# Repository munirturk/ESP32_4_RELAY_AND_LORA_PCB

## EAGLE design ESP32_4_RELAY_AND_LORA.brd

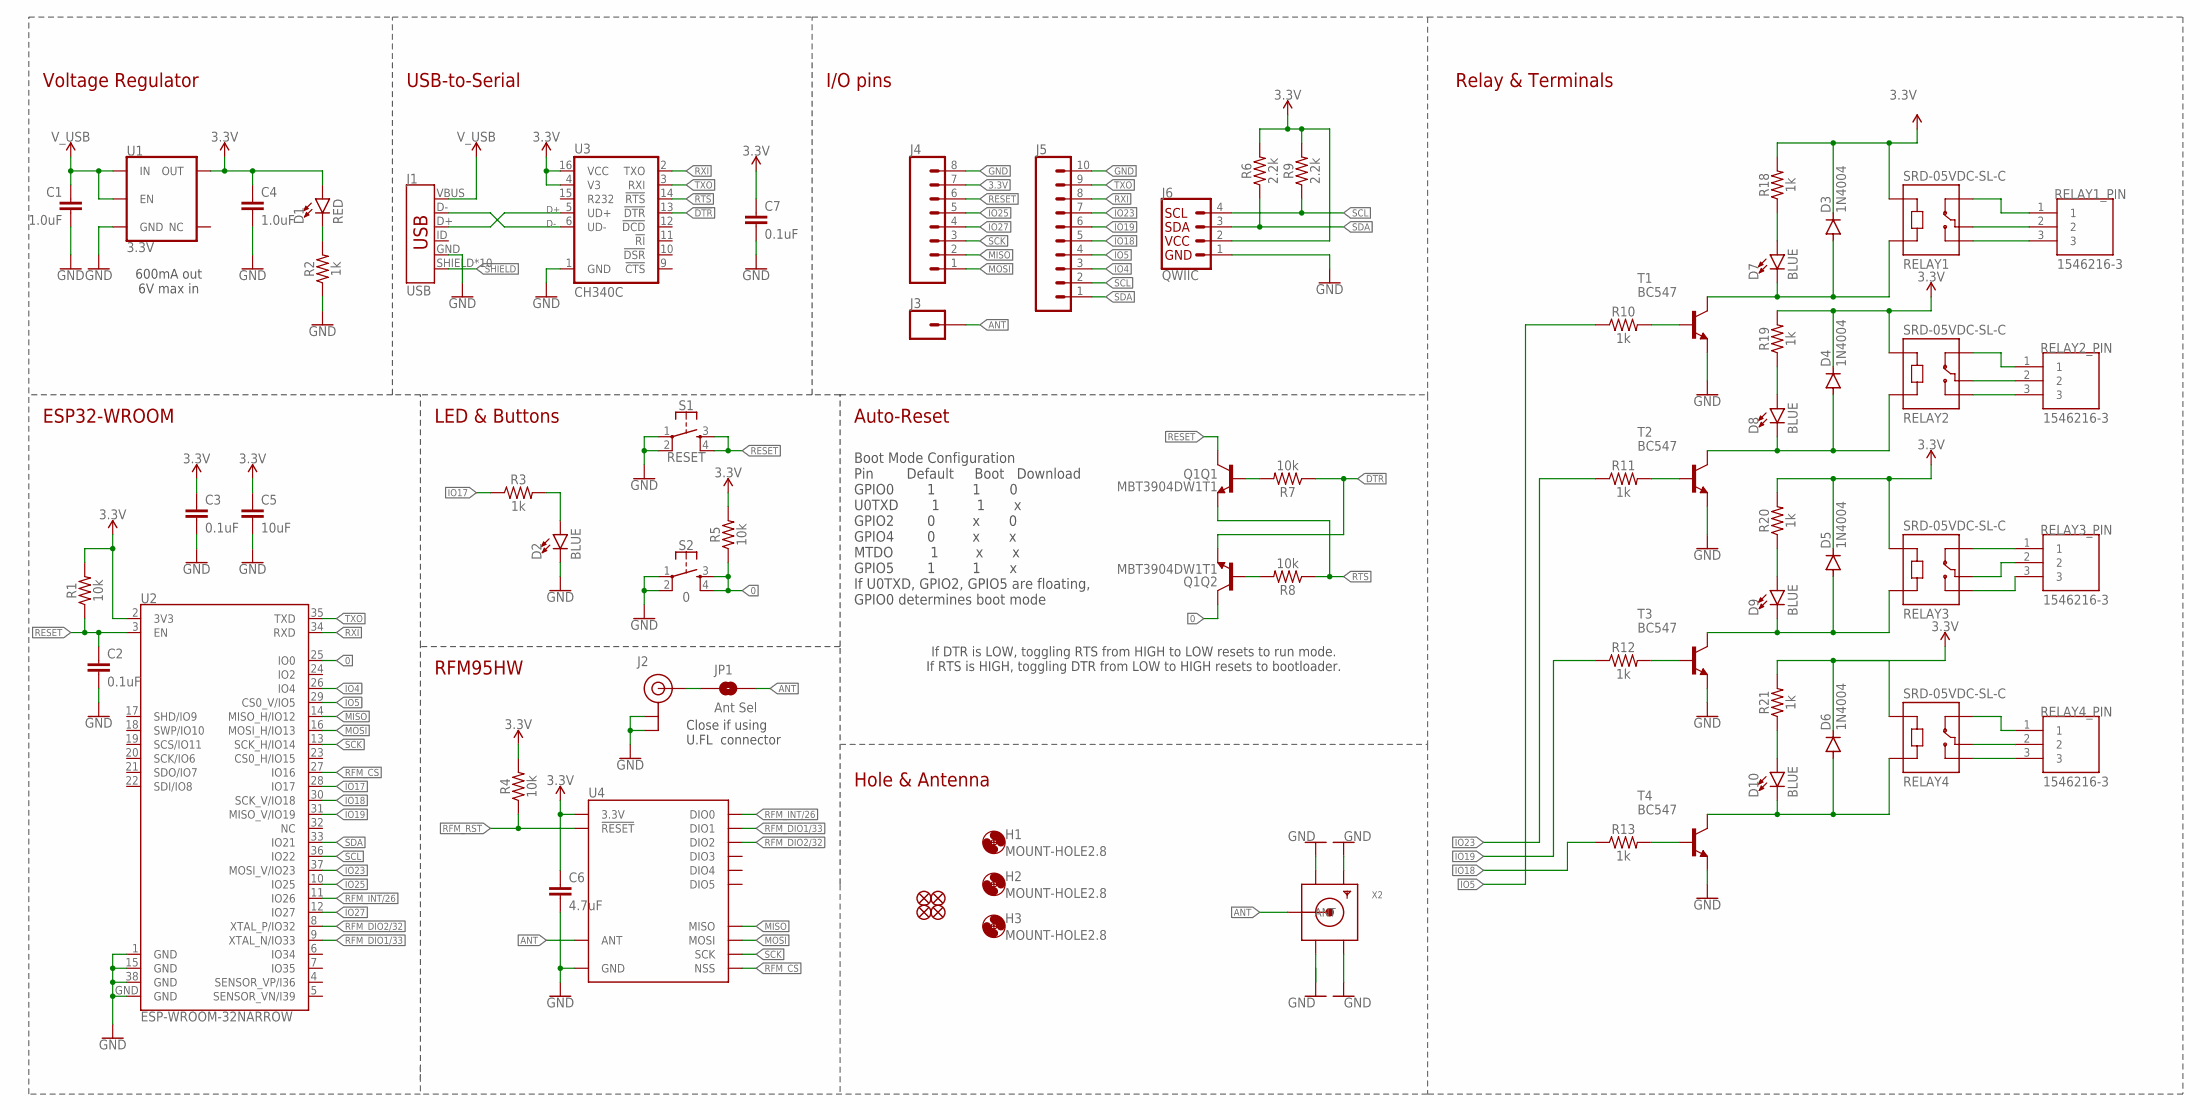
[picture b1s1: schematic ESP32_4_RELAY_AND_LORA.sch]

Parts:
C1, C4: 1.0uF; 0603
C2, C3, C7: 0.1uF; 0603
C5: 10uF; 0603
C6: 4.7uF; 0603
D1: RED; LED-0603
D2, D7, D8, D9, D10: BLUE; LED-0603
D3, D4, D5, D6: 1N4004; DO41-10
FD1, FD2, FD3, FD4: FIDUCIAL1X2; FIDUCIAL-1X2
H1, H2, H3: MOUNT-HOLE2.8; 2,8
J1: USB; USB-MICROB-PTH-MILL
J2: U.FL
J3: CONN_01PTH_NO_SILK_YES_STOP; 1X01_NO_SILK
J4: CONN_08NO_SILK_FEMALE_PTH; 1X08_NO_SILK
J5: CONN_10NO_SILK_PTH_FEMALE; 1X10_NO_SILK
J6: QWIIC; 1X04_1MM_RA
JP1: Ant Sel; SMT-JUMPER_2_NO_NO-SILK
Q1: MBT3904DW1T1; SC70-6
R1, R4, R5, R7, R8: 10k; 0603
R2, R3, R10, R11, R12, R13, R18, R19, R20, R21: 1k; 0603
R6, R9: 2.2k; 0603
RELAY1, RELAY2, RELAY3, RELAY4: SRD-05VDC-SL-C; RELAY_SRD-05VDC-SL-C
RELAY1_PIN, RELAY2_PIN, RELAY3_PIN, RELAY4_PIN: 1546216-3; TE_1546216-3
S1: RESET; TACTILE_SWITCH_SMD_4.6X2.8MM
S2: 0; TACTILE_SWITCH_SMD_4.6X2.8MM
T1, T2, T3, T4: BC547; TO92
U1: 3.3V; SOT23-5
U2: ESP-WROOM-32NARROW; ESP-WROOM-32-NARROW
U3: CH340C; SO016
U4: RFM95W; RFM95/96/97/98W
X2: SMACONNECTOR_EDGE_UFL; SMA_EDGELAUNCH_UFL

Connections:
0: Q1.6 (C), R5.1, S2.3, S2.4, U2.25 (IO0)
3.3V: C3.1, C4.1, C5.1, C6.1, C7.1, D1.A, J4.7, J6.2, R1.2, R4.2, R5.2, R6.2, R9.2, U1.5 (OUT), U2.2 (3V3), U3.4 (V3), U3.16 (VCC), U4.3.3V
!DTR: Q1.1 (E), R7.1, U3.13 (!DTR)
!RTS: Q1.4 (E), R8.1, U3.14 (!RTS)
ANT: J3.1, JP1.2, U4.ANT, X2.P (ANT)
D+: J1.D+, U3.5 (UD+)
D-: J1.D-, U3.6 (UD-)
GND: C1.2, C2.2, C3.2, C4.2, C5.2, C6.2, C7.2, D2.C, J1.GND, J2.1 (GND), J2.2 (GND), J4.8, J5.10, J6.1, R2.1, S1.1, S1.2, S2.1, S2.2, T1.1 (E), T2.1 (E), T3.1 (E), T4.1 (E), U1.2 (GND), U2.1 (GND), U2.15 (GND), U2.38 (GND), U2.GND, U3.1 (GND), U4.GND@1 (GND), U4.GND@2 (GND), U4.GND@3 (GND)
GND.2: X2.GND@1 (GND1), X2.GND@2 (GND2), X2.GND@3 (GND3), X2.GND@4 (GND4)
IO4: J5.3, U2.26 (IO4)
IO5: J5.4, R10.1, U2.29 (CS0_V/IO5)
IO17: R3.1, U2.28 (IO17)
IO18: J5.5, R13.1, U2.30 (SCK_V/IO18)
IO19: J5.6, R12.1, U2.31 (MISO_V/IO19)
IO23: J5.7, R11.1, U2.37 (MOSI_V/IO23)
IO25: J4.5, U2.10 (IO25)
IO27: J4.4, U2.12 (IO27)
MISO: J4.2, U2.14 (MISO_H/IO12), U4.MISO
MOSI: J4.1, U2.16 (MOSI_H/IO13), U4.MOSI
unnamed: D1.C, R2.2
unnamed: D2.A, R3.2
unnamed: J2.FEED (SIGNAL), JP1.1
unnamed: RELAY2.NC, RELAY2_PIN.1
unnamed: RELAY2.COM, RELAY2_PIN.2
unnamed: RELAY2.NO, RELAY2_PIN.3
unnamed: RELAY3.NC, RELAY3_PIN.1
unnamed: RELAY3.COM, RELAY3_PIN.2
unnamed: RELAY3.NO, RELAY3_PIN.3
unnamed: Q1.5 (B), R7.2
unnamed: D3.A, D7.C, RELAY1.A1, T1.3 (C)
unnamed: Q1.2 (B), R8.2
unnamed: D4.A, D8.C, RELAY2.A1, T2.3 (C)
unnamed: RELAY4.NC, RELAY4_PIN.1
unnamed: D5.A, D9.C, RELAY3.A1, T3.3 (C)
unnamed: D7.A, R18.1
unnamed: R12.2, T3.2 (B)
unnamed: D8.A, R19.1
unnamed: R11.2, T2.2 (B)
unnamed: R10.2, T1.2 (B)
unnamed: D9.A, R20.1
unnamed: RELAY4.COM, RELAY4_PIN.2
unnamed: RELAY4.NO, RELAY4_PIN.3
unnamed: RELAY1.NC, RELAY1_PIN.1
unnamed: RELAY1.COM, RELAY1_PIN.2
unnamed: RELAY1.NO, RELAY1_PIN.3
unnamed: D10.A, R21.1
unnamed: D6.A, D10.C, RELAY4.A1, T4.3 (C)
unnamed: R13.2, T4.2 (B)
unnamed: D3.C, R18.2, RELAY1.A2
unnamed: D4.C, R19.2, RELAY2.A2
unnamed: D5.C, R20.2, RELAY3.A2
unnamed: D6.C, R21.2, RELAY4.A2
RESET: C2.1, J4.6, Q1.3 (C), R1.1, S1.3, S1.4, U2.3 (EN)
RFM_CS: U2.27 (IO16), U4.NSS
RFM_DIO1/33: U2.9 (XTAL_N/IO33), U4.DIO1
RFM_DIO2/32: U2.8 (XTAL_P/IO32), U4.DIO2
RFM_INT/26: U2.11 (IO26), U4.DIO0
RFM_RST: R4.1, U4.!RESET
RXI: J5.8, U2.34 (RXD), U3.2 (TXO)
SCK: J4.3, U2.13 (SCK_H/IO14), U4.SCK
SCL: J5.2, J6.4, R9.1, U2.36 (IO22)
SDA: J5.1, J6.3, R6.1, U2.33 (IO21)
SHIELD: J1.SHIELD, J1.SHIELD2 (SHIELD), J1.SHIELD3 (SHIELD), J1.SHIELD4 (SHIELD), J1.SHIELD5 (SHIELD), J1.SHIELD6 (SHIELD), J1.SHIELD7 (SHIELD), J1.SHIELD8 (SHIELD), J1.SHIELD9 (SHIELD), J1.SHIELD10 (SHIELD)
TXO: J5.9, U2.35 (TXD), U3.3 (RXI)
V_USB: C1.1, J1.VBUS, U1.1 (IN), U1.3 (EN)

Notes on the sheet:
Boot Mode Configuration Pin Default Boot Download GPIO0 1 1 0 U0TXD 1 1 x GPIO2 0 x 0 GPIO4 0 x x MTDO 1 x x GPIO5 1 1 x If U0TXD, GPIO2, GPIO5 are floating, GPIO0 determines boot mode
If DTR is LOW, toggling RTS from HIGH to LOW resets to run mode. If RTS is HIGH, toggling DTR from LOW to HIGH resets to bootloader.
600mA out 6V max in
Voltage Regulator
USB-to-Serial
I/O pins
ESP32-WROOM
LED & Buttons
Auto-Reset
RFM95HW
Close if using U.FL connector
Relay & Terminals
Hole & Antenna

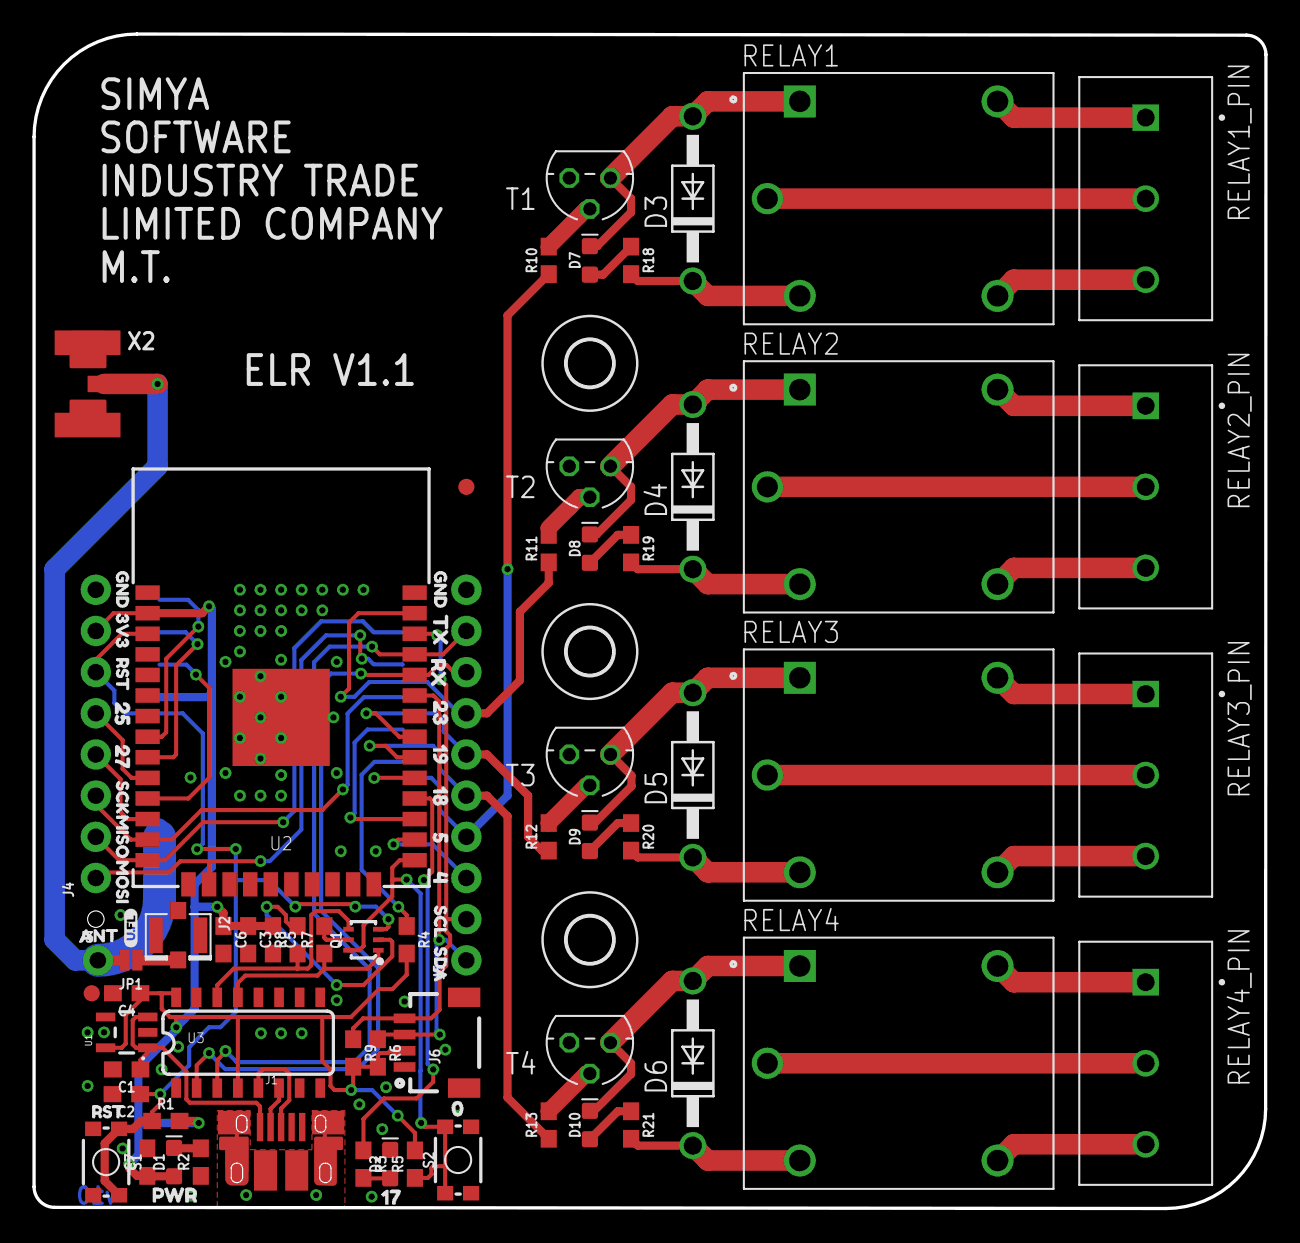
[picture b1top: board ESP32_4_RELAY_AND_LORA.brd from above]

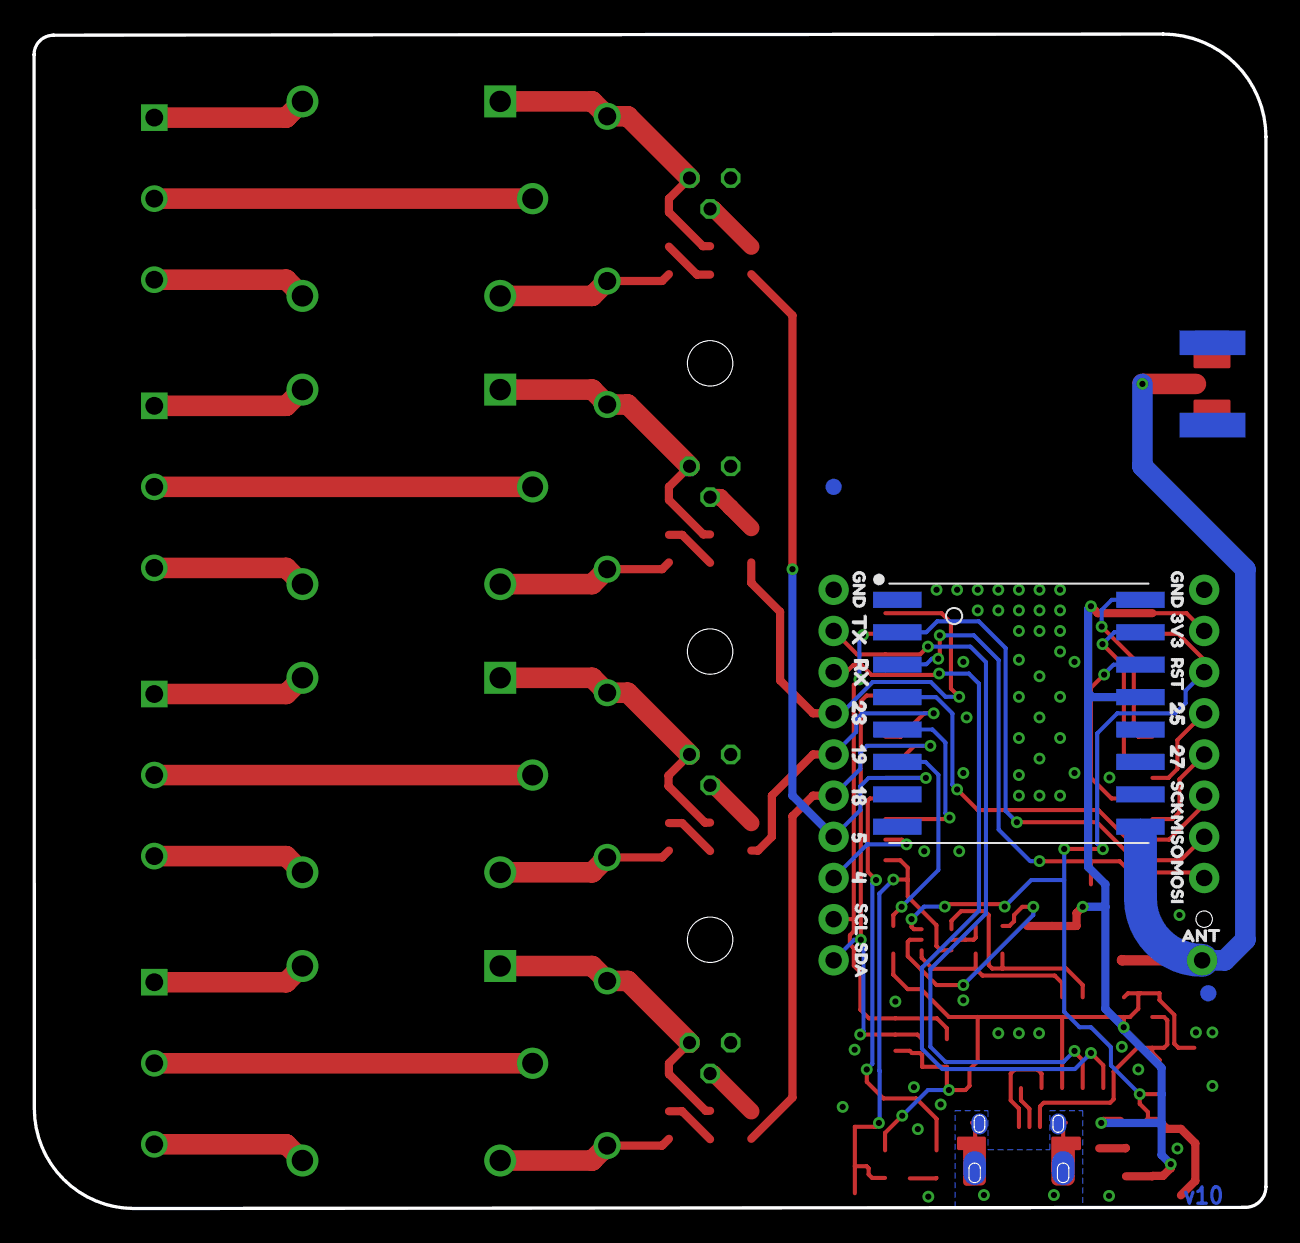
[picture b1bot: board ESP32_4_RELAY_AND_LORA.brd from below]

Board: 2 copper layers, 76.0 x 72.5 mm, 111 parts (22 on the bottom side), 65 nets.

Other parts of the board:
U$1, U$10, U$26, U$37: GND0
U$2, U$38: 3V31
U$3, U$20, U$39: RST2
U$4, U$40: 2517
U$5, U$41: 279
U$6, U$42: SCK3
U$7, U$43: MISO4
U$8, U$44: MOSI5
U$9, U$36: ANT6
U$11, U$27: TX16
U$12, U$28: RX15
U$13, U$29: 2314
U$14, U$30: 1912
U$15, U$31: 1811
U$16, U$32: 513
U$17, U$33: 410
U$18, U$34: SCL8
U$19, U$35: SDA7
U$21: 020
U$22: PWR19
U$23: 1722
U$24: U#FL0

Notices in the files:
parts and their libraries:
SparkFun-Capacitors: Licensing: Creative Commons ShareAlike 4.0 International - https://creativecommons.org/licenses/by-sa/4.0
